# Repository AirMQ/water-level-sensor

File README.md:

# water-level-sensor
Water level sensor project

# 2.0.1

# 3.0.2

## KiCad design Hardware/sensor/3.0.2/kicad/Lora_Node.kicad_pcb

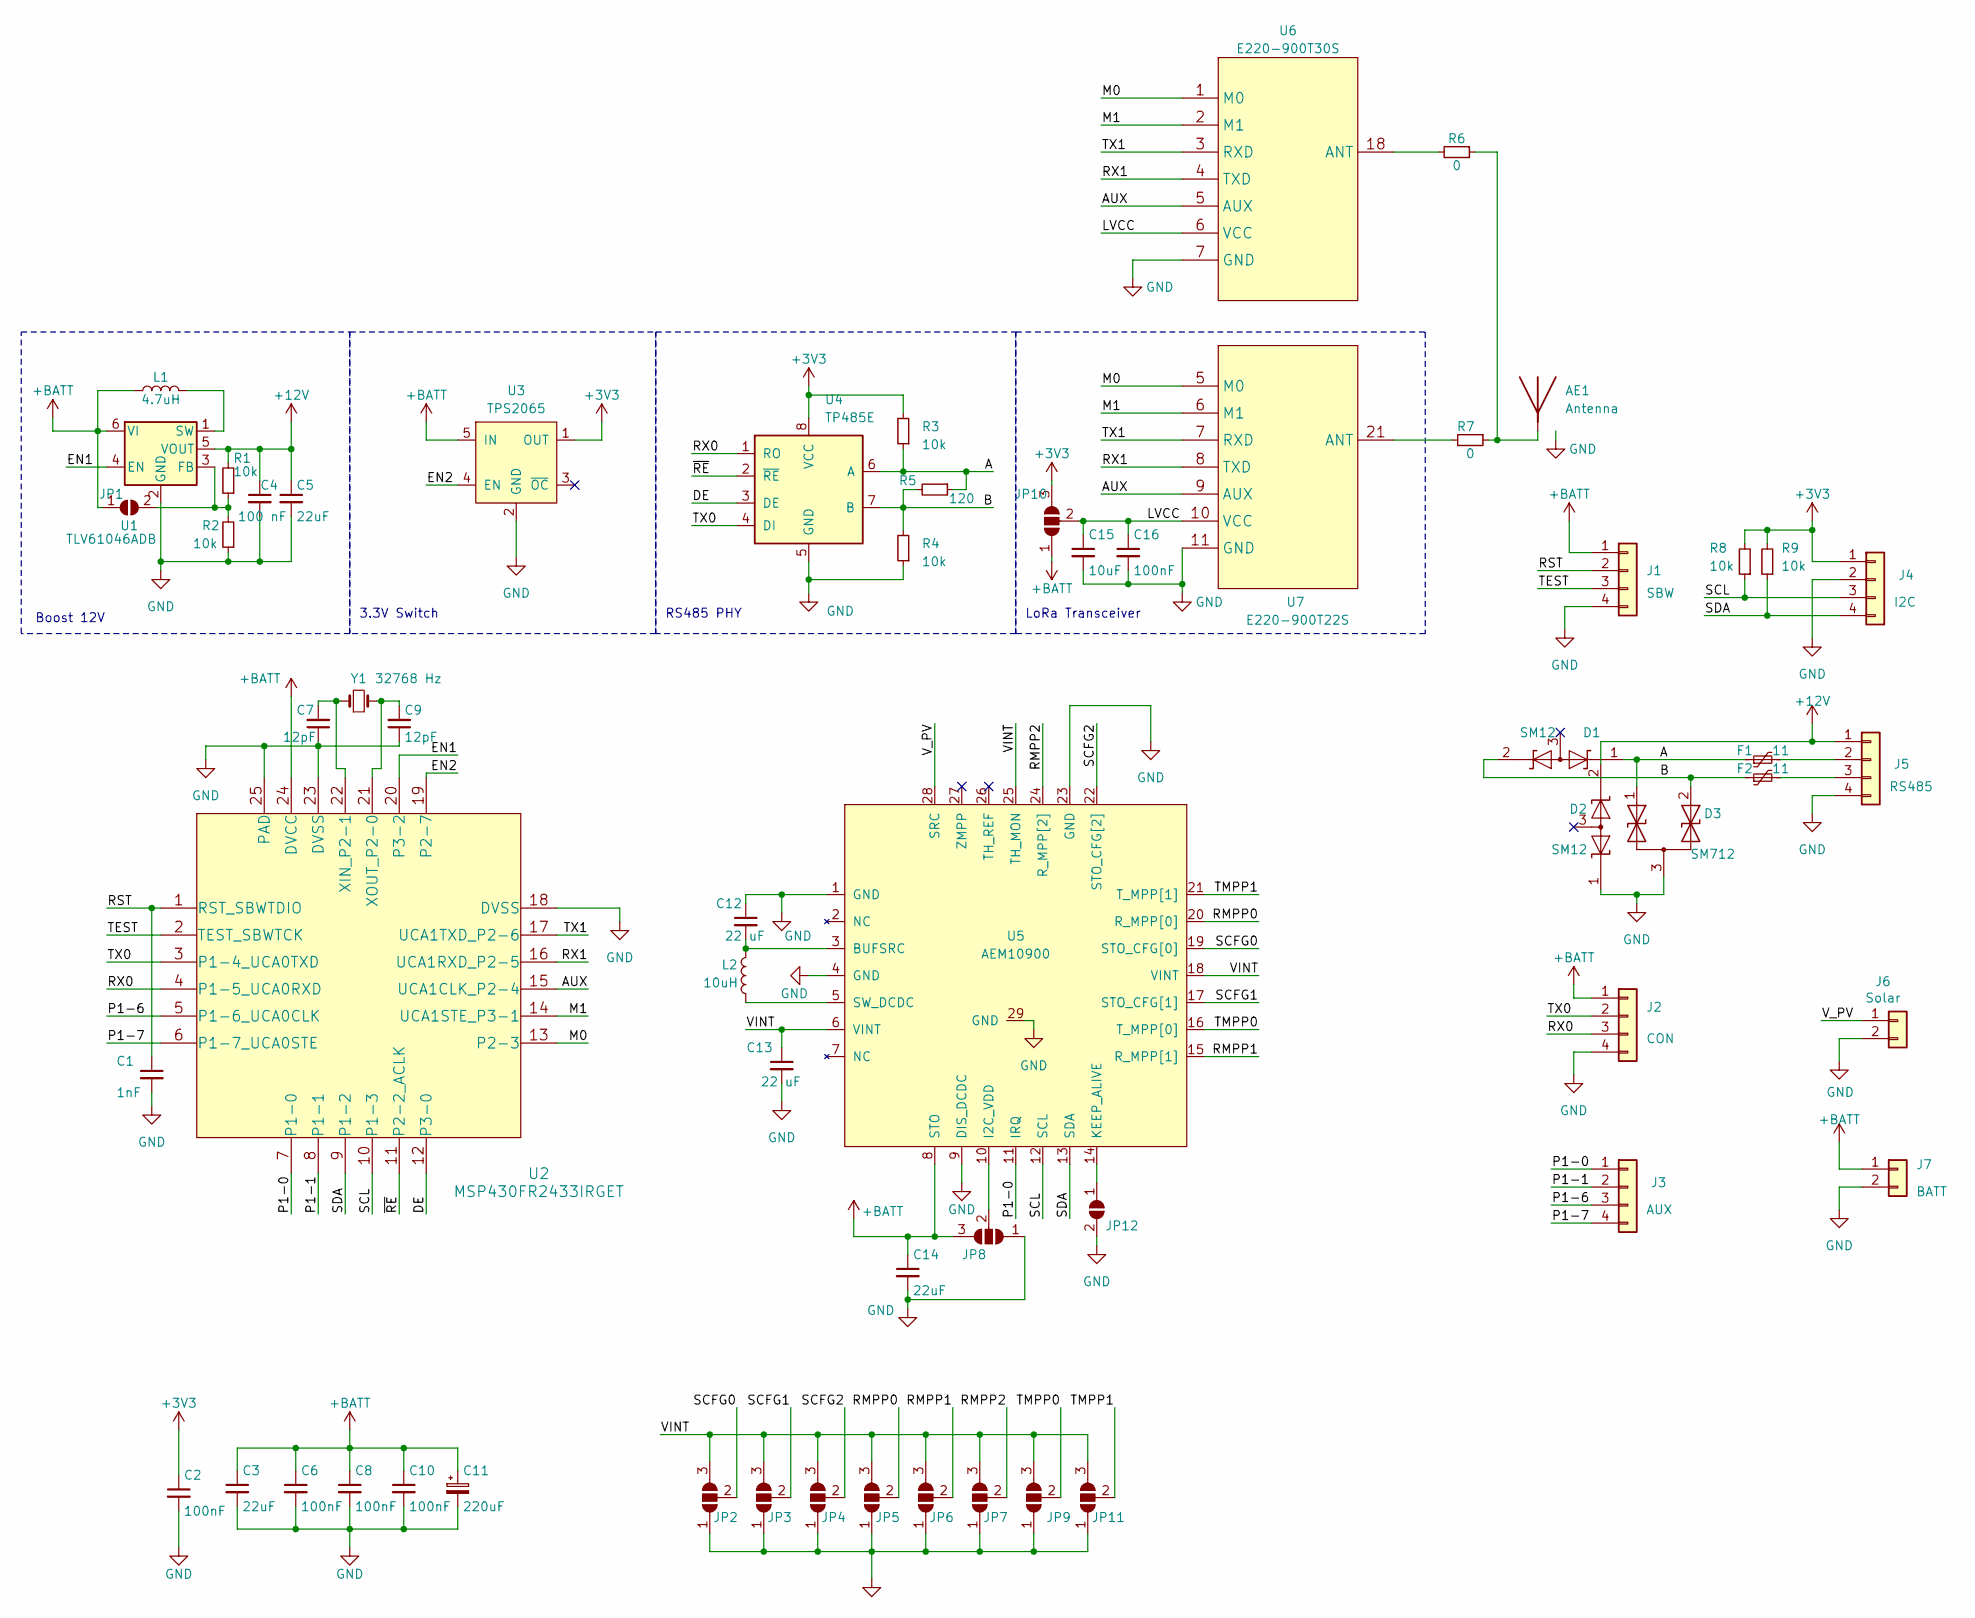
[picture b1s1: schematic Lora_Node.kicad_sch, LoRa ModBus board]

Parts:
AE1: Antenna; 868_Antenna
C1: 1nF; C_0603_1608Metric
C2, C6, C8, C10, C16: 100nF; C_0603_1608Metric
C3, C5: 22uF; C_0805_2012Metric; LCSC C98190
C4: 100 nF; C_0603_1608Metric
C7, C9: 12pF; C_0402_1005Metric
C11: 220uF; CP_EIA-3528-21_Kemet-B; LCSC C254404
C12, C13: 22 uF; C_0805_2012Metric
C14: 22uF; C_1206_3216Metric
C15: 10uF; C_0805_2012Metric; LCSC C98190
D1, D2: SM12; SOT-23; LCSC C7379974
D3: SM712; SOT-23; LCSC C521963
F1, F2: 11; Fuse_1206_3216Metric
J1: SBW; PinHeader_1x04_P2.00mm_Vertical
J2: CON; PinSocket_1x04_P2.00mm_Vertical
J3: AUX; PinSocket_1x04_P2.00mm_Vertical
J4: I2C; JST_PH_B4B-PH-K_1x04_P2.00mm_Vertical
J5: RS485; JST_PH_B4B-PH-K_1x04_P2.00mm_Vertical
J6: Solar; JST_EH_B2B-EH-A_1x02_P2.50mm_Vertical
J7: BATT; JST_EH_B2B-EH-A_1x02_P2.50mm_Vertical
JP1, JP12: SolderJumper_2_Open; SolderJumper-2_P1.3mm_Open_RoundedPad1.0x1.5mm
JP2, JP3, JP4, JP5, JP6, JP7, JP8, JP9, JP10, JP11: SolderJumper_3_Open; SolderJumper-3_P1.3mm_Open_RoundedPad1.0x1.5mm
L1: 4.7uH; CD43; LCSC C5349683
L2: 10uH; CD43
R1, R2, R3, R4, R8, R9: 10k; R_0603_1608Metric
R5: 120; R_0603_1608Metric
R6, R7: 0; R_0603_1608Metric
U1: TLV61046ADB; SOT-23-6
U2: MSP430FR2433IRGET; Texas_RGE0024H_EP2.7x2.7mm; LCSC C191026
U3: TPS2065; SOT-23-5
U4: TP485E; SOIC-8_3.9x4.9mm_P1.27mm; LCSC C7434269
U5: AEM10900; QFN-28-1EP_4x4mm_P0.4mm_EP2.6x2.6mm
U6: E220-900T30S; WIRELM-SMD_E220-900T30S
U7: E220-900T22S; WIRELM-SMD_E220-900T22S
Y1: 32768 Hz; Crystal_SMD_3215-2Pin_3.2x1.5mm; LCSC C5830645

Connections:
+3V3: C2.1, J4.1, JP10.3 (B), R3.2, R8.2, R9.2, U3.1 (OUT), U4.8 (VCC)
+12V: C4.1, C5.1, D2.2 (A2), J5.1, R1.2, U1.5 (VOUT)
+BATT: C3.1, C6.1, C8.1, C10.1, C11.1, C14.1, J1.1, J2.1, J7.1, JP1.1 (A), JP8.3 (B), JP10.1 (A), L1.1, U1.6 (VI), U2.24 (DVCC), U3.5 (IN), U5.8 (STO); also elsewhere on the board
/A: D1.1 (A1), D3.1 (A1), F1.1, R3.1, R5.1, U4.6 (A)
/AUX: U2.15 (UCA1CLK_P2-4), U6.5 (AUX), U7.9 (AUX)
/B: D1.2 (A2), D3.2 (A2), F2.1, R4.2, R5.2, U4.7 (B)
/DE: U2.12 (P3-0), U4.3 (DE)
/EN1: U1.4 (EN), U2.20 (P3-2)
/EN2: U2.19 (P2-7), U3.4 (EN)
/LVCC: C15.1, C16.1, JP10.2 (C), U6.6 (VCC), U7.10 (VCC)
/M0: U2.13 (P2-3), U6.1 (M0), U7.5 (M0)
/M1: U2.14 (UCA1STE_P3-1), U6.2 (M1), U7.6 (M1)
/P1-0: J3.1, U2.7 (P1-0), U5.11 (IRQ)
/P1-1: J3.2, U2.8 (P1-1)
/P1-6: J3.3, U2.5 (P1-6_UCA0CLK)
/P1-7: J3.4, U2.6 (P1-7_UCA0STE)
/RMPP0: JP5.2 (C), U5.20 (R_MPP[0])
/RMPP1: JP6.2 (C), U5.15 (R_MPP[1])
/RMPP2: JP7.2 (C), U5.24 (R_MPP[2])
/RST: C1.1, J1.2, U2.1 (RST_SBWTDIO)
/RX0: J2.3, U2.4 (P1-5_UCA0RXD), U4.1 (RO)
/RX1: U2.16 (UCA1RXD_P2-5), U6.4 (TXD), U7.8 (TXD)
/SCFG0: JP2.2 (C), U5.19 (STO_CFG[0])
/SCFG1: JP3.2 (C), U5.17 (STO_CFG[1])
/SCFG2: JP4.2 (C), U5.22 (STO_CFG[2])
/SCL: J4.3, R8.1, U2.10 (P1-3), U5.12 (SCL)
/SDA: J4.4, R9.1, U2.9 (P1-2), U5.13 (SDA)
/TEST: J1.3, U2.2 (TEST_SBWTCK)
/TMPP0: JP9.2 (C), U5.16 (T_MPP[0])
/TMPP1: JP11.2 (C), U5.21 (T_MPP[1])
/TX0: J2.2, U2.3 (P1-4_UCA0TXD), U4.4 (DI)
/TX1: U2.17 (UCA1TXD_P2-6), U6.3 (RXD), U7.7 (RXD)
/VINT: C13.1, JP2.3 (B), JP3.3 (B), JP4.3 (B), JP5.3 (B), JP6.3 (B), JP7.3 (B), JP9.3 (B), JP11.3 (B), U5.6 (VINT), U5.18 (VINT), U5.25 (TH_MON)
/V_PV: J6.1, U5.28 (SRC)
/~RE: U2.11 (P2-2_ACLK), U4.2 (~RE)
GND: C1.2, C2.2, C3.2, C4.2, C5.2, C6.2, C7.1, C8.2, C9.1, C10.2, C11.2, C12.1, C13.2, C14.2, C15.2, C16.2, D2.1 (A1), D3.3 (common), J1.4, J2.4, J4.2, J5.4, J6.2, J7.2, JP2.1 (A), JP3.1 (A), JP4.1 (A), JP5.1 (A), JP6.1 (A), JP7.1 (A), JP8.1 (A), JP9.1 (A), JP11.1 (A), JP12.2 (B), R2.1, R4.1, U1.2 (GND), U2.18 (DVSS), U2.23 (DVSS), U2.25 (PAD), U3.2 (GND), U4.5 (GND), U5.1 (GND), U5.4 (GND), U5.9 (DIS_DCDC), U5.23 (GND), U5.29 (GND), U6.7 (GND), U6.9 (GND), U6.15 (GND), U6.16 (GND), U6.17 (GND), U7.1 (GND), U7.2 (GND), U7.3 (GND), U7.4 (GND), U7.11 (GND), U7.13 (GND), U7.19 (GND), U7.20 (GND), U7.22 (GND); also elsewhere on the board
unnamed: AE1.1 (A), R6.1, R7.1
unnamed: F1.2, J5.2
unnamed: F2.2, J5.3
unnamed: JP1.2 (B), R1.1, R2.2, U1.3 (FB)
unnamed: JP8.2 (C), U5.10 (I2C_VDD)
unnamed: JP12.1 (A), U5.14 (KEEP_ALIVE)
unnamed: L1.2, U1.1 (SW)
unnamed: C7.2, U2.22 (XIN_P2-1), Y1.1
unnamed: C9.2, U2.21 (XOUT_P2-0), Y1.2
unnamed: C12.2, L2.2, U5.3 (BUFSRC)
unnamed: L2.1, U5.5 (SW_DCDC)
unnamed: R6.2, U6.18 (ANT)
unnamed: R7.2, U7.21 (ANT)

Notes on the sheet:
3.3V Switch
LoRa Transceiver
RS485 PHY
Boost 12V

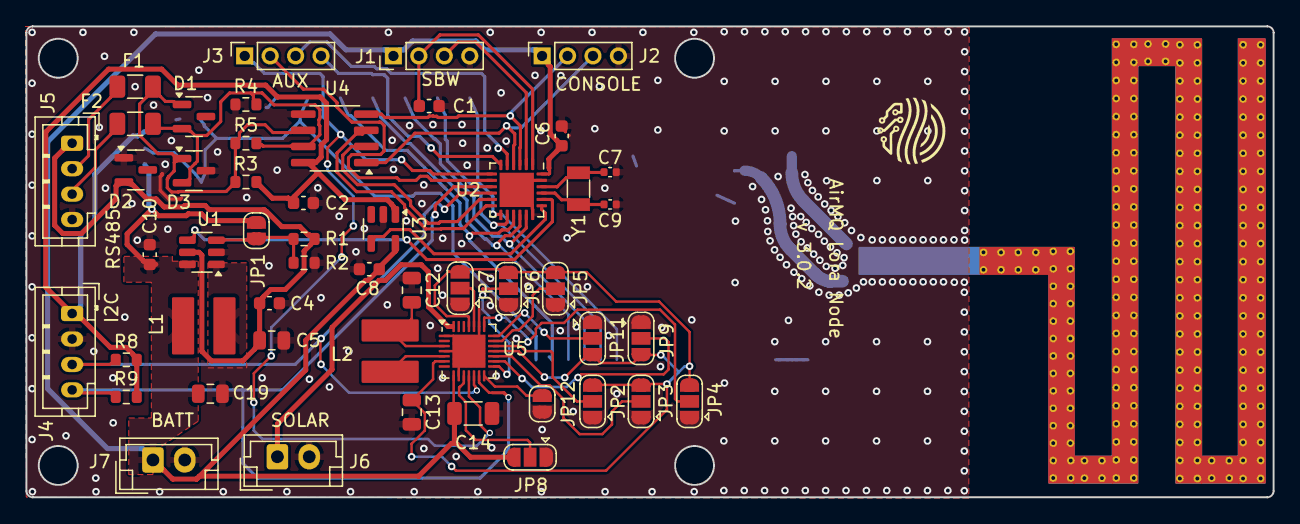
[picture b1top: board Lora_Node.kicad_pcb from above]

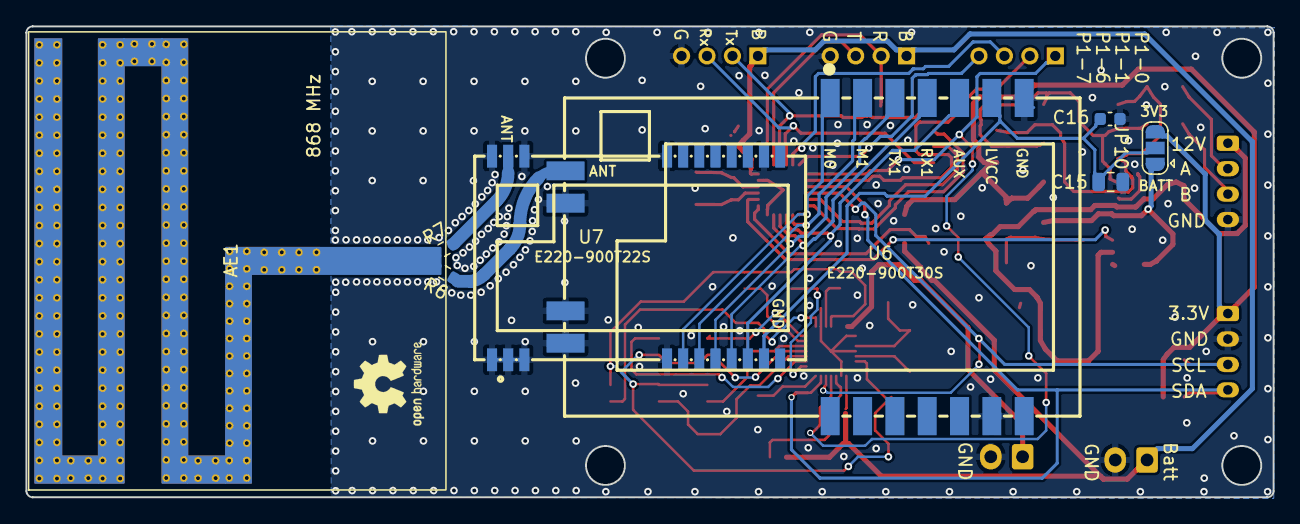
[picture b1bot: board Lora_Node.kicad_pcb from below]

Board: 2 copper layers, 98.0 x 37.0 mm, 60 parts (8 on the bottom side), 49 nets.

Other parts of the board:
586: AirMQ_Logo; AirMQ_Logo_005
C19: 100nF; C_0805_2012Metric

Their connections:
+BATT: C19.1; also elsewhere on the board
GND: C19.2; also elsewhere on the board

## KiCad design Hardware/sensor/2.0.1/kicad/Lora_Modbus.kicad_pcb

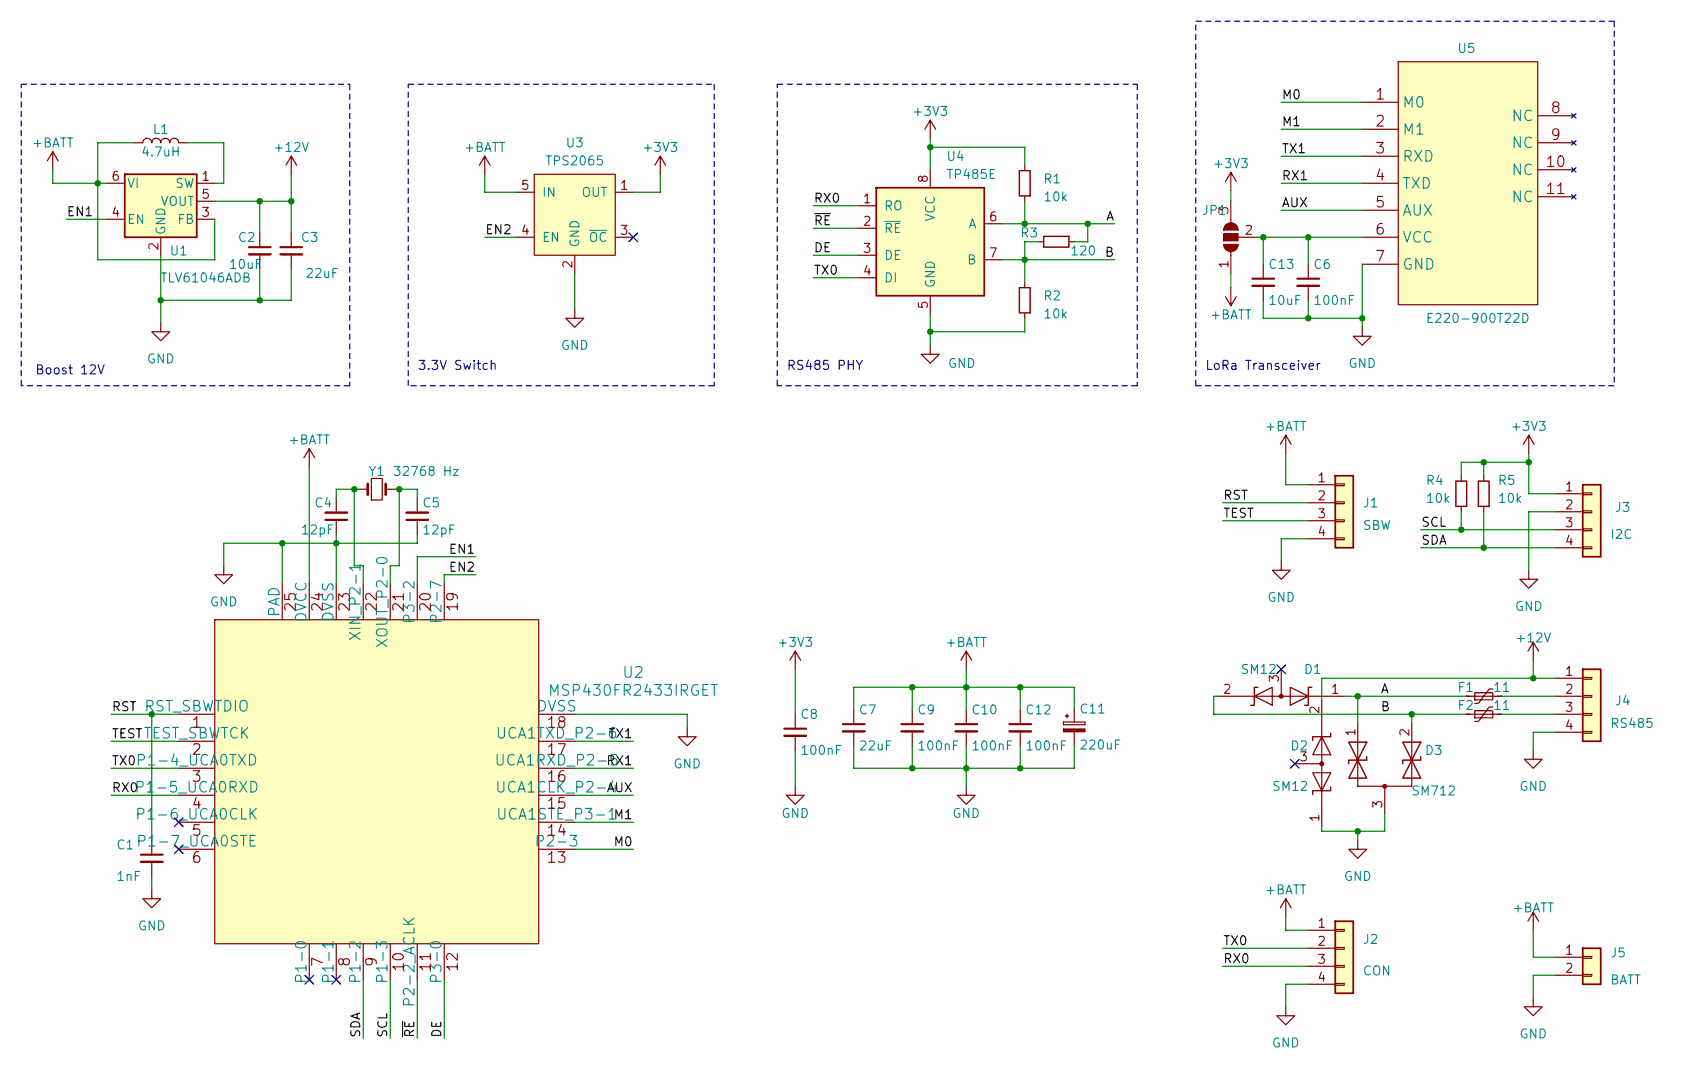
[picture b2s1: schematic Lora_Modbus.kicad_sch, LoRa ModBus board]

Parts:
C1: 1nF; C_0603_1608Metric
C2: 10uF; C_0603_1608Metric
C3, C7: 22uF; C_0805_2012Metric; LCSC C98190
C4, C5: 12pF; C_0402_1005Metric
C6, C8, C9, C10, C12: 100nF; C_0603_1608Metric
C11: 220uF; CP_EIA-3528-21_Kemet-B; LCSC C254404
C13: 10uF; C_0805_2012Metric; LCSC C98190
D1, D2: SM12; SOT-23; LCSC C7379974
D3: SM712; SOT-23; LCSC C521963
F1, F2: 11; Fuse_1206_3216Metric
J1: SBW; PinHeader_1x04_P2.00mm_Vertical
J2: CON; PinSocket_1x04_P2.00mm_Vertical
J3: I2C; JST_PH_B4B-PH-K_1x04_P2.00mm_Vertical
J4: RS485; JST_PH_B4B-PH-K_1x04_P2.00mm_Vertical
J5: BATT; JST_EH_B2B-EH-A_1x02_P2.50mm_Vertical
JP1: SolderJumper_3_Open; SolderJumper-3_P1.3mm_Open_RoundedPad1.0x1.5mm
L1: 4.7uH; CD43; LCSC C5349683
R1, R2, R4, R5: 10k; R_0603_1608Metric
R3: 120; R_0603_1608Metric
U1: TLV61046ADB; SOT-23-6
U2: MSP430FR2433IRGET; Texas_RGE0024H_EP2.7x2.7mm; LCSC C191026
U3: TPS2065; SOT-23-5
U4: TP485E; SOIC-8_3.9x4.9mm_P1.27mm; LCSC C7434269
U5: E220-900T22D; E220T22D
Y1: 32768 Hz; Crystal_SMD_3215-2Pin_3.2x1.5mm; LCSC C5830645

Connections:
+3V3: C8.1, J3.1, JP1.3 (B), R1.2, R4.2, R5.2, U3.1 (OUT), U4.8 (VCC)
+12V: C2.1, C3.1, D2.2 (A2), J4.1, U1.5 (VOUT)
+BATT: C7.1, C9.1, C10.1, C11.1, C12.1, J1.1, J2.1, J5.1, JP1.1 (A), L1.1, U1.3 (FB), U1.6 (VI), U2.24 (DVCC), U3.5 (IN)
/A: D1.1 (A1), D3.1 (A1), F1.1, R1.1, R3.1, U4.6 (A)
/AUX: U2.15 (UCA1CLK_P2-4), U5.5 (AUX)
/B: D1.2 (A2), D3.2 (A2), F2.1, R2.2, R3.2, U4.7 (B)
/DE: U2.12 (P3-0), U4.3 (DE)
/EN1: U1.4 (EN), U2.20 (P3-2)
/EN2: U2.19 (P2-7), U3.4 (EN)
/M0: U2.13 (P2-3), U5.1 (M0)
/M1: U2.14 (UCA1STE_P3-1), U5.2 (M1)
/RST: C1.1, J1.2, U2.1 (RST_SBWTDIO)
/RX0: J2.3, U2.4 (P1-5_UCA0RXD), U4.1 (RO)
/RX1: U2.16 (UCA1RXD_P2-5), U5.4 (TXD)
/SCL: J3.3, R4.1, U2.10 (P1-3)
/SDA: J3.4, R5.1, U2.9 (P1-2)
/TEST: J1.3, U2.2 (TEST_SBWTCK)
/TX0: J2.2, U2.3 (P1-4_UCA0TXD), U4.4 (DI)
/TX1: U2.17 (UCA1TXD_P2-6), U5.3 (RXD)
/~RE: U2.11 (P2-2_ACLK), U4.2 (~RE)
GND: C1.2, C2.2, C3.2, C4.1, C5.1, C6.2, C7.2, C8.2, C9.2, C10.2, C11.2, C12.2, C13.2, D2.1 (A1), D3.3 (common), J1.4, J2.4, J3.2, J4.4, J5.2, R2.1, U1.2 (GND), U2.18 (DVSS), U2.23 (DVSS), U2.25 (PAD), U3.2 (GND), U4.5 (GND), U5.7 (GND)
unnamed: F1.2, J4.2
unnamed: F2.2, J4.3
unnamed: C6.1, C13.1, JP1.2 (C), U5.6 (VCC)
unnamed: L1.2, U1.1 (SW)
unnamed: C4.2, U2.22 (XIN_P2-1), Y1.1
unnamed: C5.2, U2.21 (XOUT_P2-0), Y1.2

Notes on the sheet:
3.3V Switch
LoRa Transceiver
RS485 PHY
Boost 12V

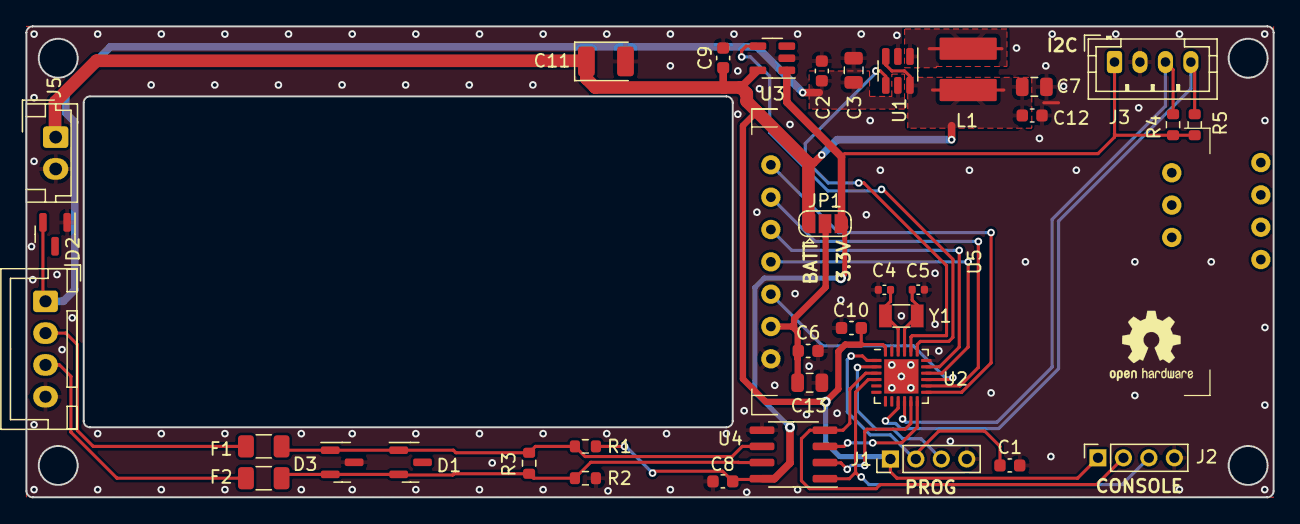
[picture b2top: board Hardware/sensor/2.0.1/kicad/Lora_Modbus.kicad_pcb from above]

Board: 2 copper layers, 98.0 x 37.0 mm, 36 parts (1 on the bottom side), 25 nets.

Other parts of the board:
586: AirMQ_Logo; AirMQ_Logo_01

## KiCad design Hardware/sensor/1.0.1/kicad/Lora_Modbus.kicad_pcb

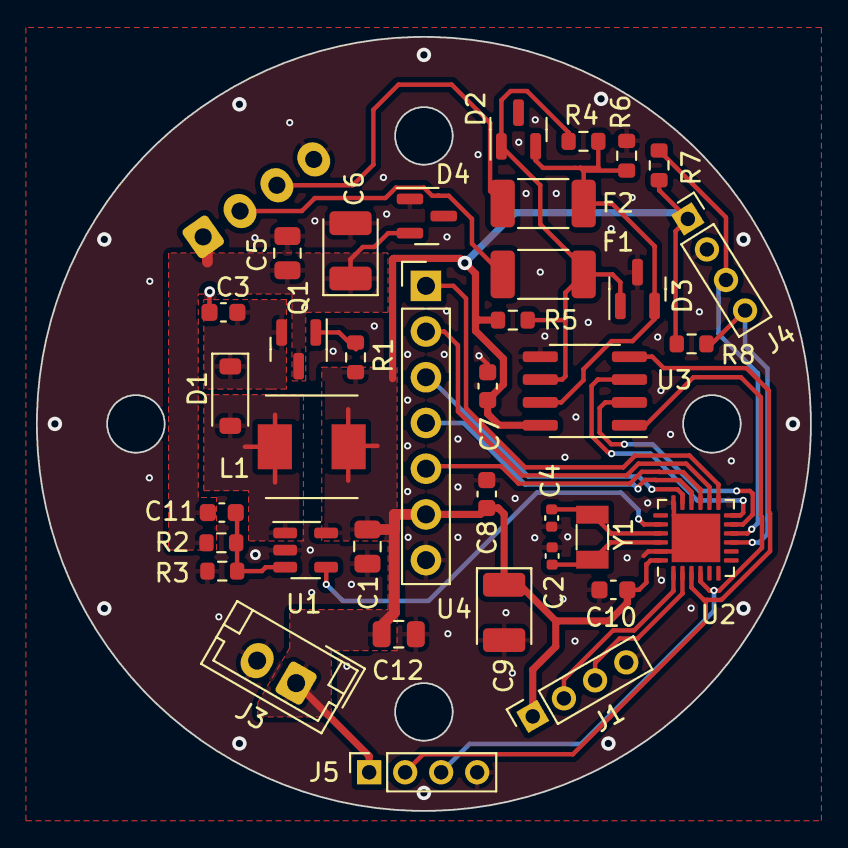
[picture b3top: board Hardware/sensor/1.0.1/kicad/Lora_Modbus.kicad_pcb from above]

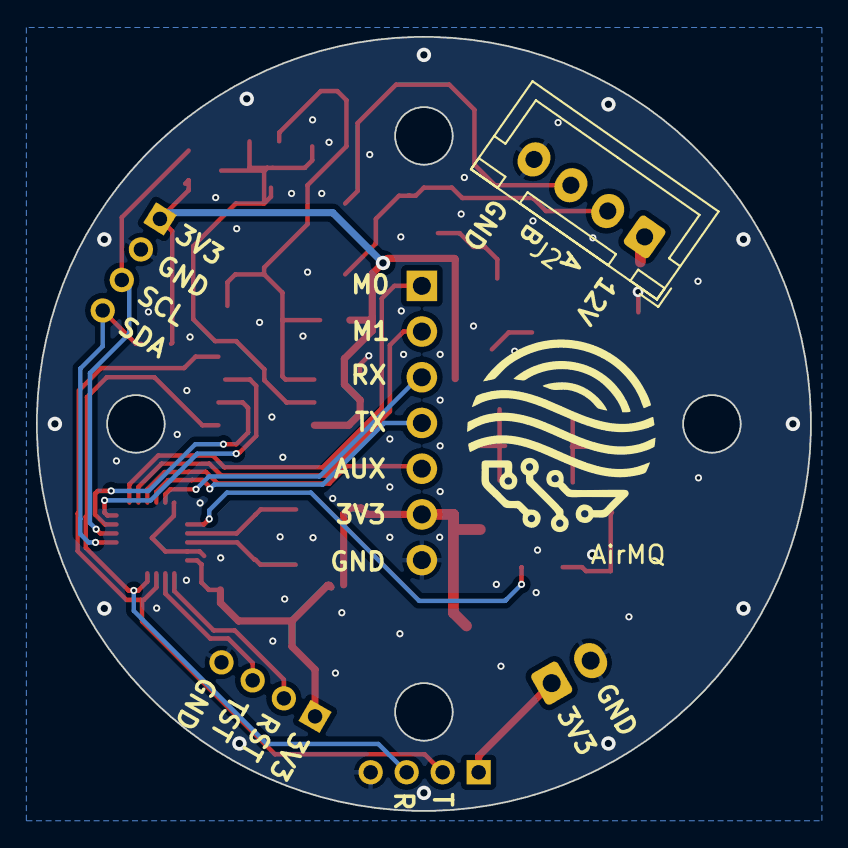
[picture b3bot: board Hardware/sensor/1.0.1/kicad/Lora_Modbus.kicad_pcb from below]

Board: 2 copper layers, 43.0 x 43.0 mm, 39 parts (2 on the bottom side), 27 nets.

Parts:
586: AirMQ_Logo; AirMQ_Logo_01
C1, C5: 22uF; C_0805_2012Metric
C2, C4: 12pF; C_0402_1005Metric
C3: 10uF; C_0603_1608Metric
C6: 47uF; CP_EIA-3528-21_Kemet-B
C7, C8, C10: 100nF; C_0603_1608Metric
C9: 220uF; CP_EIA-3528-21_Kemet-B
C11: 22pF; C_0603_1608Metric
C12: 10uF; C_0805_2012Metric
D1: MBR0530; D_SOD-123
D2, D4: SM12; SOT-23
D3: SM712; SOT-23
F1, F2: 11; Fuse_2010_5025Metric
J1, J4, J5: Conn_01x04; PinSocket_1x04_P2.00mm_Vertical
J2: Conn_01x04; JST_XH_B4B-XH-A_1x04_P2.50mm_Vertical
J3: Conn_01x02; JST_EH_B2B-EH-A_1x02_P2.50mm_Vertical
L1: 4.7uH; Inductor_0530
Q1: Si2371EDS; SOT-23
R1: 100; R_0603_1608Metric
R2: 1.6M; R_0603_1608Metric
R3: 180k; R_0603_1608Metric
R4: 120; R_0603_1608Metric
R5, R6, R7, R8: 10k; R_0603_1608Metric
U1: TPS61040DBV; SOT-23-5
U2: MSP430FR2433IRGET; Texas_RGE0024H_EP2.7x2.7mm
U3: SP3485EN; SOIC-8_3.9x4.9mm_P1.27mm
U4: E220-900T22D; PinHeader_1x07_P2.54mm_Vertical
Y1: Crystal_GND24; Crystal_SMD_3215-2Pin_3.2x1.5mm

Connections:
+3V3: C1.1, C7.1, C8.1, C9.1, C10.1, C12.1, J1.1, J3.1, J4.1, J5.1, R1.1, R5.2, R7.2, R8.2, U1.5 (VIN), U2.24 (DVCC), U3.8 (VCC), U4.6 (VCC)
+12V: C5.1, C6.1, C11.1, D4.2 (A2), J2.1, Q1.3 (D), R2.2
/A: D2.1 (A1), D3.1 (A1), F1.1, R4.1, R5.1, U3.6 (A)
/AUX: U2.15 (UCA1CLK_P2-4), U4.5 (AUX)
/B: D2.2 (A2), D3.2 (A2), F2.1, R4.2, R6.2, U3.7 (B)
/DE: U2.12 (P3-0), U3.3 (DE)
/EN: U1.4 (EN), U2.20 (P3-2)
/M0: U2.13 (P2-3), U4.1 (M0)
/M1: U2.14 (UCA1STE_P3-1), U4.2 (M1)
/RST: J1.2, U2.1 (RST_SBWTDIO)
/RX0: J5.3, U2.4 (P1-5_UCA0RXD), U3.1 (RO)
/RX1: U2.16 (UCA1RXD_P2-5), U4.4 (TXD)
/SCL: J4.3, R7.1, U2.10 (P1-3)
/SDA: J4.4, R8.1, U2.9 (P1-2)
/TEST: J1.3, U2.2 (TEST_SBWTCK)
/TX0: J5.2, U2.3 (P1-4_UCA0TXD), U3.4 (DI)
/TX1: U2.17 (UCA1TXD_P2-6), U4.3 (RXD)
/~RE: U2.11 (P2-2_ACLK), U3.2 (~RE)
GND: C1.2, C2.1, C3.2, C4.1, C5.2, C6.2, C7.2, C8.2, C9.2, C10.2, C12.2, D3.3 (common), D4.1 (A1), J1.4, J2.4, J3.2, J4.2, J5.4, R3.1, R6.1, U1.2 (GND), U2.18 (DVSS), U2.23 (DVSS), U2.25 (PAD), U3.5 (GND), U4.7 (GND)
unnamed: D1.2 (A), U1.1 (SW)
unnamed: C3.1, D1.1 (K), Q1.2 (S)
unnamed: F1.2, J2.2
unnamed: F2.2, J2.3
unnamed: Q1.1 (G), R1.2
unnamed: C11.2, R2.1, R3.2, U1.3 (FB)
unnamed: C2.2, U2.22 (XIN_P2-1), Y1.1
unnamed: C4.2, U2.21 (XOUT_P2-0), Y1.2

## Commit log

2024-05-02 added pdf board image
2024-05-02 added PCB board image
2024-05-02 added PDF schematic
2024-05-02 added schematic
2024-05-02 added 3D model
2024-05-02 Create dir
2025-12-01 Create 1
